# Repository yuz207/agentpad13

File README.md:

# agentpad13

A 13-key macropad for agentic work, designed from scratch: RP2040, USB-C, 12×1U + 1×2U hot-swap
keys, a clickable EC11 encoder, an analog tilt joystick, a capacitive-touch key, and 24 RGB LEDs
(per-key plus edge underglow) that an open Raw HID protocol drives to show what your agents are
doing — thinking, running, waiting, done, one key each.

## Build one

### → [Open the configurator](https://yuz207.github.io/agentpad13/configurator/site/)

Pick your options, turn the pad around in 3D, and get back an order sheet where every line links to
the exact file you upload to a fab or drop into a slicer. That is the way in. Prefer paper?
[`release/HOW-TO-ORDER.md`](release/HOW-TO-ORDER.md) is the same thing, static.

<p align="center"><sub>The shipping v5 board in the v2 case, straight from the CAD.</sub></p>

## What is where

```
release/            The bundle — everything you order, print or flash.
  HOW-TO-ORDER.md     The configurator's static form.
  RELEASE.md          What shipped and why, section by section.
  MANIFEST.md         Every file in the bundle with its md5 and byte count.
  hardware/           Board fab package, case, plate, bases, keycaps, toppers, gasket.
  firmware/           Flashable UF2s, BRING-UP.md, POLARITY-NOTE.md.
configurator/       The published site and its consumption assets; current outputs are copied from development.
firmware/           vial-qmk tree, simulations, conformance tests, BUILD.md.
docs/               The Raw HID protocol contract, and the design reviews.
```

Before you send anything to a fab, run `python3 manifest_selfverify.py` — it should print
**9/9 checks PASS**. Every listed file is present with the right hash, and nothing unlisted is
hiding in the bundle.

## Printed toppers already? Print them again

The v1 encoder knobs and stick caps are retired. The current release carries three Ø17.5 encoder
knob styles and three joystick toppers: a compact nub, restored TPU puck, and a conventional Ø12
topper paired with a TPU restrictor. Details are in [`release/RELEASE.md`](release/RELEASE.md) §(f).

## Status

- **PCB — complete.** v5_8, 84.2 × 100 mm, 2-layer, DRC clean, fab package ready to upload. It retains the v5.7 LED correction, adds the Ø4.0 TP5 solder landing, and factory-populates the encoder.
- **Case — complete.** v2.17: FR4 or printed plate, band in three sidewalls, printed tray.
- **Bases — complete.** Three optional printed bases; the case is finished without one.
- **Firmware — validated.** Emulator-booted and protocol-conformant. Flash `agentpad13.uf2`.
- **Configurator — live.** Static files: no build step, no network calls, no dependencies.

### AgentPad13 Direct OAI (experimental alternative)

The isolated `codex_oai` keymap is an experimental alternative for direct
Codex Desktop control. It is not Vial firmware and does not replace the normal,
recommended `release/firmware/prebuilt/agentpad13.uf2`. Codex Desktop talks to
this target directly—no helper, daemon, bridge, or Vial protocol—using the
locked `Codex Micro Lab OAI LED` identity (`303A:8360`, usage `FF00:61`, Report
ID 6, 64-byte reports).

The current unflashed candidate is
`release/firmware/prebuilt/agentpad13_codex_oai.uf2`, 93,696 bytes, SHA-256
`fcb50b2419419be43b7cf90b00a96b16063fcaf182bc24b9642d57e2e8adf54d`.
Start with the [keymap contract](firmware/loudest_micro/keymaps/codex_oai/README.md),
[source hand-off](firmware/CODEX-OAI-SOURCE.md), and
[Direct OAI build procedure](firmware/BUILD.md#agentpad13-direct-oai-experimental-alternative).
Run the complete host suite from the repository root:

```sh
python3 -m unittest discover -s firmware/tests/codex_oai -p 'test_*.py'
```

The checked-in [emulator capture](firmware/evidence/codex-oai-emulator.json)
and [current manifest](firmware/evidence/codex-oai-current-manifest.json) bind
that exact UF2 to the offline USB/protocol/LED checks. Physical validation is
still entirely PENDING; no install or flash occurred. Any future hardware
operation requires the literal authorization and observation record in the
[physical runbook](docs/codex-oai-physical-runbook.md).

## First power-on

Flash [`agentpad13.uf2`](release/firmware/prebuilt/agentpad13.uf2) — hold BOOTSEL and drag the file on. Then hold
SW14, the button in the back, for about a second and follow the 13 key LEDs: the board measures its
own joystick and stores the result. About 15 seconds, no host software, no reflash, once ever —
full procedure in [`release/firmware/BRING-UP.md`](release/firmware/BRING-UP.md). If an axis reads
backwards that is polarity, not calibration:
[`release/firmware/POLARITY-NOTE.md`](release/firmware/POLARITY-NOTE.md).

Firmware source is in [`firmware/loudest_micro/`](firmware/loudest_micro/); the exact Vial/QMK
build recipe and validation commands are in [`firmware/BUILD.md`](firmware/BUILD.md). The plain-QMK,
byte-reproducible build is [`agentpad13_reference.uf2`](release/firmware/prebuilt/agentpad13_reference.uf2).

## Licensing

- `release/hardware/` — **CERN-OHL-W-2.0** (PCB and case CAD).
- `firmware/` and `release/firmware/` — **GPL-2.0-or-later** (QMK/vial-qmk
  derivative), except `firmware/tests/conformance/protocol_oracle.py`, which is
  **MIT**. Corresponding source for the prebuilt UF2s = this tree built against
  [vial-qmk](https://github.com/vial-kb/vial-qmk) per `firmware/BUILD.md`.

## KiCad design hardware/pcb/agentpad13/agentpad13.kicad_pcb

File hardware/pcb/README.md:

# agentpad13 — PCB (v5, complete)

Finished, fabrication-ready 2-layer RP2040 macropad PCB. Designed in **KiCad 9**.

- **Outline:** 84.2 × 100 mm octagon (chamfered), 1.6 mm FR-4, 2 layers.
- **DRC:** clean — **0 violations, 0 unconnected** at a 0.152 mm / 6-mil standard
  fab tier (min via drill 0.20 mm).
- **Function:** 13 hot-swap keys (12×1U + 1×2U), EC11 encoder + push, analog
  2-axis tilt joystick (YTL YA13), TTP223 capacitive touch key, and a 24-LED
  SK6812 chain (14 reverse-mount top LEDs incl. 1 layer indicator + 10
  side/underglow LEDs) level-shifted for a 5 V VBUS rail. All SMD reflow parts
  are on the back (B.Cu); the joystick is a machine-placed through-hole part
  on the front.
- **v5 vs Rev A:** the encoder moved so its shaft centers on the case plate's
  encoder opening, the USB-C receptacle was flipped 180° so its mouth faces the
  case wall aperture, and the hand-solder PSP-slider joystick was replaced by
  the fab-placed YA13 tilt gimbal (LCSC C37323742) with datasheet-verified
  wiring — see `renders/js1_detail.png` and `../../firmware/POLARITY-NOTE.md`
  for the one-time axis/calibration config note.

## Board revision — v5_7 (current)

The published board is **v5_7**. It differs from **v5_6**, the revision the first
units were built from, by **two footprint rotations and nothing else**: the
bottom-edge underglow LEDs **LED20** and **LED21** were rotated 180° so they fire
*into* the board instead of off the edge. Same positions, same layer, same nets, no
part changes — both BOMs and the opaque SKU's pick-and-place file are byte-identical
to v5_6, and the translucent CPL differs in exactly those two rows (`Rot 0 → 180`).

Why they were wrong: the board generator applies each underglow LED's rotation and
*then* flips the part to the back copper, and that flip negates orientation. The two
pairs aimed along Y reversed; the left and right rails, aimed along X, survived. The
result was six of the ten side LEDs firing inward and four firing outward.

**`LED15`/`LED16`, beside the USB connector, still fire outward — that is
deliberate.** They wash the surface behind the pad and are kept that way by choice.
The shipping board is 8 inward / 2 outward.

If you have a board built from v5_6, nothing is broken and nothing needs reworking:
four of the ten underglow LEDs simply throw their light off the edge rather than
under the case.

## Files

```
agentpad13/                 the KiCad 9 project
  agentpad13.kicad_pcb      board
  agentpad13.kicad_sch      schematic
  agentpad13.kicad_pro      project
  fp-lib-table              footprint library table (KIPRJMOD-relative)
lib/                        vendored footprint libraries (see lib/LIBS.md)
BOM.csv                     full bill of materials (MPN / LCSC / DigiKey, pricing)
gerbers.zip                 bare-board manufacturing files (Gerbers + drill)
fabpack_opaque.zip          opaque SKU: gerbers + assembly CSVs + ORDERING.md
fabpack_translucent.zip     translucent SKU: gerbers + assembly CSVs + ORDERING.md
assembly/                   loose per-SKU assembly files
  cpl_opaque.csv            pick-and-place, opaque SKU      (90 placements)
  cpl_translucent.csv       pick-and-place, translucent SKU (110 placements)
  bom_opaque.csv            assembly BOM, opaque SKU
  bom_translucent.csv       assembly BOM, translucent SKU
  hand_solder_afterlist.csv the parts you hand-solder after the boards arrive
renders/                    top.png, bottom.png (v5_7), js1_detail.png (joystick
                            close-up; still the v5_6 plot — the revision changed
                            nothing at that end of the board)
```

## Two SKUs, one bare board

The bare PCB is **identical** for both SKUs — only which parts get placed differs:

| SKU | Top shell | Underglow (LED15-24 + C40-49) |
|---|---|---|
| **opaque** (Rev A default) | solid | not populated (DNP) |
| **translucent** | glowing diffuser | populated |

## Ordering

Upload **`gerbers.zip`** to the bare-board quote and the matching SKU's
`assembly/cpl_<sku>.csv` + `assembly/bom_<sku>.csv` to turnkey (consigned)
assembly — **single side** (bottom SMD; the joystick is a fab-placed
through-hole part). Each `fabpack_*.zip` bundles the Gerbers, that SKU's
assembly CSVs, and a full step-by-step `ORDERING.md` (board options, tier
guidance, DNP handling, pricing ballpark, and pre-order gates). The repo-root
`HOW-TO-ORDER.md` is the condensed walk-through.

**LED cut-outs are intentional:** the Edge.Cuts layer has 14 small internal
rounded-rectangle windows (one per top LED) so the reverse-mounted LEDs shine
through the board — not an outline error.

## Hand-soldered afterlist

The fab places everything else — including the JS1 joystick, a machine-placed
through-hole YA13 (its wiring is datasheet-verified; no metering needed). You
hand-solder (see `assembly/hand_solder_afterlist.csv`):

- **RE1** — EC11 rotary encoder + push (through-hole). Seat it flush.
- Optionally the 13 hot-swap sockets (SW1-13) and 2 tact switches (SW14/15) if you
  opt out of fab assembly for them — they are fab-placed by default.

At first power-on, if the stick drives the cursor opposite to your push, that is
the expected 180°-clocking polarity — a one-line config fix per axis, described
with the calibration note in `../../firmware/POLARITY-NOTE.md`.

## Firmware / GPIO note

The firmware pin map (`firmware/loudest_micro/`) matches the v5 board (identical
to Rev A v4 — the v5 changes needed zero firmware edits) and has been
validated — it boots in an RP2040 emulator and its Raw HID status protocol is
conformance-tested. See `firmware/FIRMWARE-V4-NOTES.md` and `firmware/tests/`.

## License

Hardware (schematic, PCB): **CERN-OHL-W-2.0**. Vendored footprint libraries keep
their upstream licenses (marbastlib: CERN-OHL-P v2; MX_V2: MIT) — see `lib/LIBS.md`.

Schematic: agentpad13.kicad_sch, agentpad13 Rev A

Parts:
C1, C2, C3, C4, C5, C6, C7, C8, C9, C10, C13, C20, C21, C22, C23, C24, C26, C27, C28, C29, C30, C31, C32, C33, C34, C35, C36, C37, C38, C39, C40, C41, C42, C43, C44, C45, C46, C47, C48, C49: 100n; C_0402_1005Metric; MPN CL05B104KO5NNNC; LCSC C1525
C11, C12, C14, C15: 1u; C_0402_1005Metric; MPN CL05A105KA5NNNC; LCSC C52923
C16, C17: 10u; C_0805_2012Metric; MPN CL21A106KOQNNNE; LCSC C15850
C18, C19: 15p; C_0402_1005Metric; MPN CL05C150JB5NNNC; LCSC C1548
C25: DNP; C_0402_1005Metric; MPN C_0402; JLC Basic; not fitted
D1: SD05C; D_SOD-323; MPN SD05C; LCSC C1884584; not fitted
F1: 750mA; Fuse_1812_4532Metric; MPN MF-MSMF075/24-2; LCSC C208467
FB1: 600R@100MHz; L_0402_1005Metric; MPN BLM15AG601SN1D; LCSC C76884
J1: USB-C; USB_C_Receptacle_HRO_TYPE-C-31-M-12; MPN TYPE-C-31-M-12; LCSC C165948
J2: EXPANSION; PinHeader_1x08_P2.54mm_Vertical; MPN PinHeader_1x08; JLC n/a; not fitted
JS1: YA13-FL7.4-B5Ka; YA13-FL7.4-B5Ka_C37323742; MPN YA13-FL7.4-B5Ka(45-10)-R-Y06; LCSC C37323742
LED1, LED2, LED3, LED4, LED5, LED6, LED7, LED8, LED9, LED10, LED11, LED12, LED13, LED14: SK6812MINI-E; LED_6028R; MPN SK6812MINI-E; LCSC C5149201
LED15, LED16, LED17, LED18, LED19, LED20, LED21, LED22, LED23, LED24: SK6812-SIDE; LED_WS2812_4020; MPN SK6812SIDE-A; LCSC C5378721
R1, R2: 5.1k; R_0402_1005Metric; MPN 0402WGF5101TCE; LCSC C25905
R3, R4: 27; R_0402_1005Metric; MPN 0402WGF270JTCE; LCSC C25100
R5, R6, R11, R12: 1k; R_0402_1005Metric; MPN 0402WGF1001TCE; LCSC C11702
R7: 10k; R_0402_1005Metric; MPN 0402WGF1002TCE; LCSC C25744
R8, R9: 4.7k; R_0402_1005Metric; MPN 0402WGF4701TCE; LCSC C25900
R10: 0R; R_0402_1005Metric; MPN 0402WGF0000TCE; LCSC C17168
RE1: EC11; RotaryEncoder_Alps_EC11E-Switch_Vertical_H20mm; MPN PEC11R-4215F-S0024; LCSC C143790
SW1, SW2, SW3, SW4, SW5, SW6, SW7, SW8, SW9, SW10, SW11, SW12, SW13: MX_Hotswap; SW_MX_HS_CPG151101S11_1u; MPN Kailh_CPG151101S11; LCSC C41430893
SW14: BOOT; SW_SPST_PTS645Sx43SMTR92; MPN PTS645SM43SMTR92 LFS; LCSC C221880
SW15: RESET; SW_SPST_PTS645Sx43SMTR92; MPN PTS645SM43SMTR92 LFS; LCSC C221880
TP1: SWCLK; TestPoint_Pad_D1.5mm; MPN TestPad; JLC n/a
TP2: SWDIO; TestPoint_Pad_D1.5mm; MPN TestPad; JLC n/a
TP3: 3V3; TestPoint_Pad_D1.5mm; MPN TestPad; JLC n/a
TP4: GND; TestPoint_Pad_D1.5mm; MPN TestPad; JLC n/a
TP5: TOUCHPAD; TestPoint_Pad_D1.5mm; MPN CopperPour; JLC n/a
U1: RP2040; QFN-56-1EP_7x7mm_P0.4mm_EP3.2x3.2mm; MPN RP2040; LCSC C2040
U2: W25Q128JVSIQ; SOIC-8_5.3x5.3mm_P1.27mm; MPN W25Q128JVSIQ; LCSC C97521
U3: AP2112K-3.3; SOT-23-5; MPN AP2112K-3.3TRG1; LCSC C51118
U4: USBLC6-2SC6; SOT-23-6; MPN USBLC6-2SC6; LCSC C7519
U5: SN74LVC1T45; SOT-23-6; MPN SN74LVC1T45DBVR; LCSC C7843
U6: TTP223; SOT-23-6; MPN TTP223-BA6; LCSC C42422127
Y1: 12MHz ABM8-272-T3; Crystal_SMD_3225-4Pin_3.2x2.5mm; MPN ABM8-272-T3; LCSC C20625731

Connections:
+1V1: C7.1, C8.1, C12.1, U1.23 (DVDD), U1.45 (VREG_VOUT), U1.50 (DVDD)
+3V3: C1.1, C2.1, C3.1, C4.1, C5.1, C6.1, C10.1, C11.1, C13.1, C15.1, C17.1, C20.1, C22.1, FB1.1, J2.1, JS1.1 (XA), JS1.4 (YA), R7.1, R8.1, R9.1, TP3.1, U1.1 (IOVDD), U1.10 (IOVDD), U1.22 (IOVDD), U1.33 (IOVDD), U1.42 (IOVDD), U1.44 (VREG_VIN), U1.48 (USB_VDD), U1.49 (IOVDD), U2.8 (VCC), U3.5 (VOUT), U5.1 (VCCA), U5.5 (DIR), U6.5 (VDD)
+5V: C14.1, C16.1, C21.1, C26.1, C27.1, C28.1, C29.1, C30.1, C31.1, C32.1, C33.1, C34.1, C35.1, C36.1, C37.1, C38.1, C39.1, C40.1, C41.1, C42.1, C43.1, C44.1, C45.1, C46.1, C47.1, C48.1, C49.1, D1.2 (K), F1.2, J2.8, LED1.1 (VDD), LED2.1 (VDD), LED3.1 (VDD), LED4.1 (VDD), LED5.1 (VDD), LED6.1 (VDD), LED7.1 (VDD), LED8.1 (VDD), LED9.1 (VDD), LED10.1 (VDD), LED11.1 (VDD), LED12.1 (VDD), LED13.1 (VDD), LED14.1 (VDD), LED15.2 (VDD), LED16.2 (VDD), LED17.2 (VDD), LED18.2 (VDD), LED19.2 (VDD), LED20.2 (VDD), LED21.2 (VDD), LED22.2 (VDD), LED23.2 (VDD), LED24.2 (VDD), U3.1 (VIN), U3.3 (EN), U4.5 (VBUS), U5.6 (VCCB)
ADC_AVDD: C9.1, FB1.2, U1.43 (ADC_AVDD)
BOOTSEL: R6.2, SW14.1
CC1: J1.A5 (CC1), R1.1
CC2: J1.B5 (CC2), R2.1
DM: R4.2, U1.46 (USB_DM)
DP: R3.2, U1.47 (USB_DP)
ENC_A: RE1.A, U1.16 (GPIO13)
ENC_B: RE1.B, U1.17 (GPIO14)
ENC_SW: RE1.S1, U1.18 (GPIO15)
GND: C1.2, C2.2, C3.2, C4.2, C5.2, C6.2, C7.2, C8.2, C9.2, C10.2, C11.2, C12.2, C13.2, C14.2, C15.2, C16.2, C17.2, C18.2, C19.2, C20.2, C21.2, C22.2, C23.2, C24.2, C25.2, C26.2, C27.2, C28.2, C29.2, C30.2, C31.2, C32.2, C33.2, C34.2, C35.2, C36.2, C37.2, C38.2, C39.2, C40.2, C41.2, C42.2, C43.2, C44.2, C45.2, C46.2, C47.2, C48.2, C49.2, D1.1 (A), J1.A1 (GND), J1.A12 (GND), J1.B1 (GND), J1.B12 (GND), J1.S1 (SHIELD), J2.2, JS1.3 (XB), JS1.6 (YB), JS1.MP1, JS1.MP2, JS1.MP3, JS1.MP4, LED1.4 (VSS), LED2.4 (VSS), LED3.4 (VSS), LED4.4 (VSS), LED5.4 (VSS), LED6.4 (VSS), LED7.4 (VSS), LED8.4 (VSS), LED9.4 (VSS), LED10.4 (VSS), LED11.4 (VSS), LED12.4 (VSS), LED13.4 (VSS), LED14.4 (VSS), LED15.4 (VSS), LED16.4 (VSS), LED17.4 (VSS), LED18.4 (VSS), LED19.4 (VSS), LED20.4 (VSS), LED21.4 (VSS), LED22.4 (VSS), LED23.4 (VSS), LED24.4 (VSS), R1.2, R2.2, R10.2, RE1.C, RE1.S2, SW1.2, SW2.2, SW3.2, SW4.2, SW5.2, SW6.2, SW7.2, SW8.2, SW9.2, SW10.2, SW11.2, SW12.2, SW13.2, SW14.2, SW15.2, TP4.1, U1.19 (TESTEN), U1.57 (GND), U2.4 (GND), U3.2 (GND), U4.2 (GND), U5.2 (GND), U6.2 (VSS), U6.6 (TOG), Y1.2, Y1.4
GP20: J2.5, U1.31 (GPIO20)
GP21: J2.6, U1.36 (GPIO24)
GP28: J2.7, U1.40 (GPIO28_ADC2)
JOY_X: JS1.2 (XW), R11.1
JOY_X_ADC: C23.1, R11.2, U1.38 (GPIO26_ADC0)
JOY_Y: JS1.5 (YW), R12.1
JOY_Y_ADC: C24.1, R12.2, U1.39 (GPIO27_ADC1)
PORT_DM: J1.A7 (DN1), J1.B7 (DN2), U4.4 (IO2)
PORT_DP: J1.A6 (DP1), J1.B6 (DP2), U4.6 (IO1)
QSPI_CLK: U1.52 (QSPI_SCLK), U2.6 (CLK)
QSPI_CS: R6.1, U1.56 (QSPI_SS_N), U2.1 (~CS)
QSPI_SD0: U1.53 (QSPI_SD0), U2.5 (DI_IO0)
QSPI_SD1: U1.55 (QSPI_SD1), U2.2 (DO_IO1)
QSPI_SD2: U1.54 (QSPI_SD2), U2.3 (~WP_IO2)
QSPI_SD3: U1.51 (QSPI_SD3), U2.7 (~HOLD_IO3)
RGB_D00: LED1.3 (DIN), U5.4 (B)
RGB_D01: LED1.2 (DOUT), LED2.3 (DIN)
RGB_D02: LED2.2 (DOUT), LED3.3 (DIN)
RGB_D03: LED3.2 (DOUT), LED4.3 (DIN)
RGB_D04: LED4.2 (DOUT), LED5.3 (DIN)
RGB_D05: LED5.2 (DOUT), LED6.3 (DIN)
RGB_D06: LED6.2 (DOUT), LED7.3 (DIN)
RGB_D07: LED7.2 (DOUT), LED8.3 (DIN)
RGB_D08: LED8.2 (DOUT), LED9.3 (DIN)
RGB_D09: LED9.2 (DOUT), LED10.3 (DIN)
RGB_D10: LED10.2 (DOUT), LED11.3 (DIN)
RGB_D11: LED11.2 (DOUT), LED12.3 (DIN)
RGB_D12: LED12.2 (DOUT), LED13.3 (DIN)
RGB_D13: LED13.2 (DOUT), LED14.3 (DIN)
RGB_D14: LED14.2 (DOUT), LED15.1 (DIN)
RGB_D15: LED15.3 (DOUT), LED16.1 (DIN)
RGB_D16: LED16.3 (DOUT), LED17.1 (DIN)
RGB_D17: LED17.3 (DOUT), LED18.1 (DIN)
RGB_D18: LED18.3 (DOUT), LED19.1 (DIN)
RGB_D19: LED19.3 (DOUT), LED20.1 (DIN)
RGB_D20: LED20.3 (DOUT), LED21.1 (DIN)
RGB_D21: LED21.3 (DOUT), LED22.1 (DIN)
RGB_D22: LED22.3 (DOUT), LED23.1 (DIN)
RGB_D23: LED23.3 (DOUT), LED24.1 (DIN)
RGB_MCU: U1.28 (GPIO17), U5.3 (A)
RUN: R7.2, SW15.1, U1.26 (RUN)
SCL: J2.4, R9.2, U1.30 (GPIO19)
SDA: J2.3, R8.2, U1.29 (GPIO18)
SW1: SW1.1, U1.15 (GPIO12)
SW2: SW2.1, U1.12 (GPIO9)
SW3: SW3.1, U1.7 (GPIO5)
SW4: SW4.1, U1.4 (GPIO2)
SW5: SW5.1, U1.14 (GPIO11)
SW6: SW6.1, U1.11 (GPIO8)
SW7: SW7.1, U1.6 (GPIO4)
SW8: SW8.1, U1.3 (GPIO1)
SW9: SW9.1, U1.13 (GPIO10)
SW10: SW10.1, U1.9 (GPIO7)
SW11: SW11.1, U1.5 (GPIO3)
SW12: SW12.1, U1.2 (GPIO0)
SW13: SW13.1, U1.8 (GPIO6)
SWCLK: TP1.1, U1.24 (SWCLK)
SWDIO: TP2.1, U1.25 (SWDIO)
TOUCH_AHLB: R10.1, U6.4 (AHLB)
TOUCH_OUT: U1.27 (GPIO16), U6.1 (Q)
TOUCH_PAD: C25.1, TP5.1, U6.3 (I)
USB_DM: R4.1, U4.3 (IO2)
USB_DP: R3.1, U4.1 (IO1)
VBUS: F1.1, J1.A4 (VBUS), J1.A9 (VBUS), J1.B4 (VBUS), J1.B9 (VBUS)
XIN: C18.1, U1.20 (XIN), Y1.1
XOUT: R5.1, U1.21 (XOUT)
XOUT_XTAL: C19.1, R5.2, Y1.3

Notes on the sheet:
agentpad13 Rev A flat schematic (auto-generated). Connectivity is by net-name labels; footprints bound at layout.

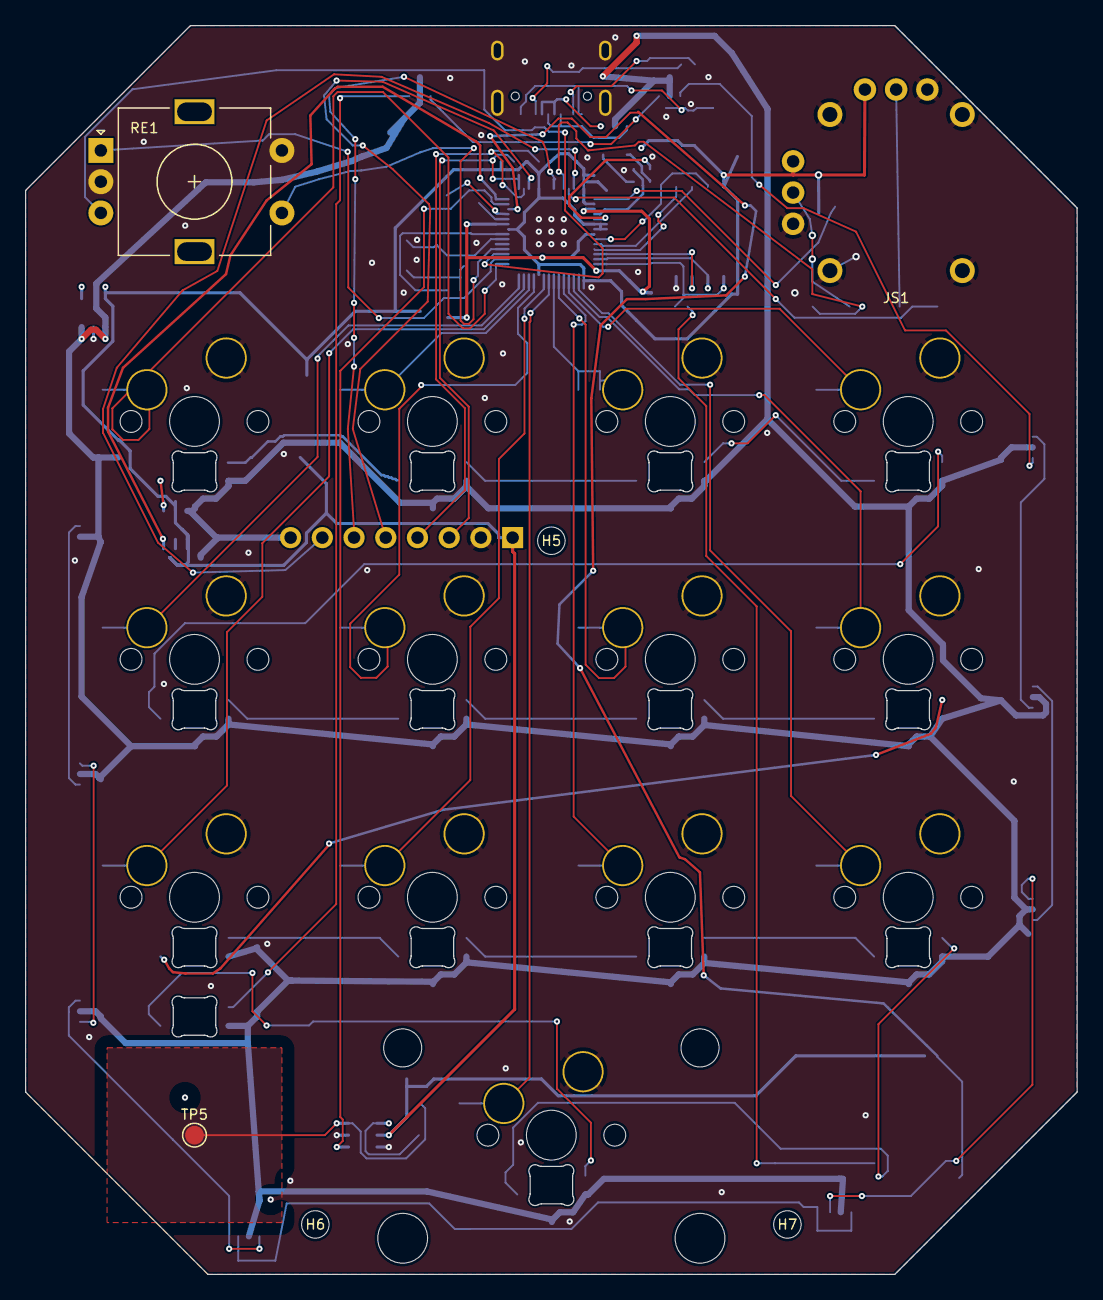
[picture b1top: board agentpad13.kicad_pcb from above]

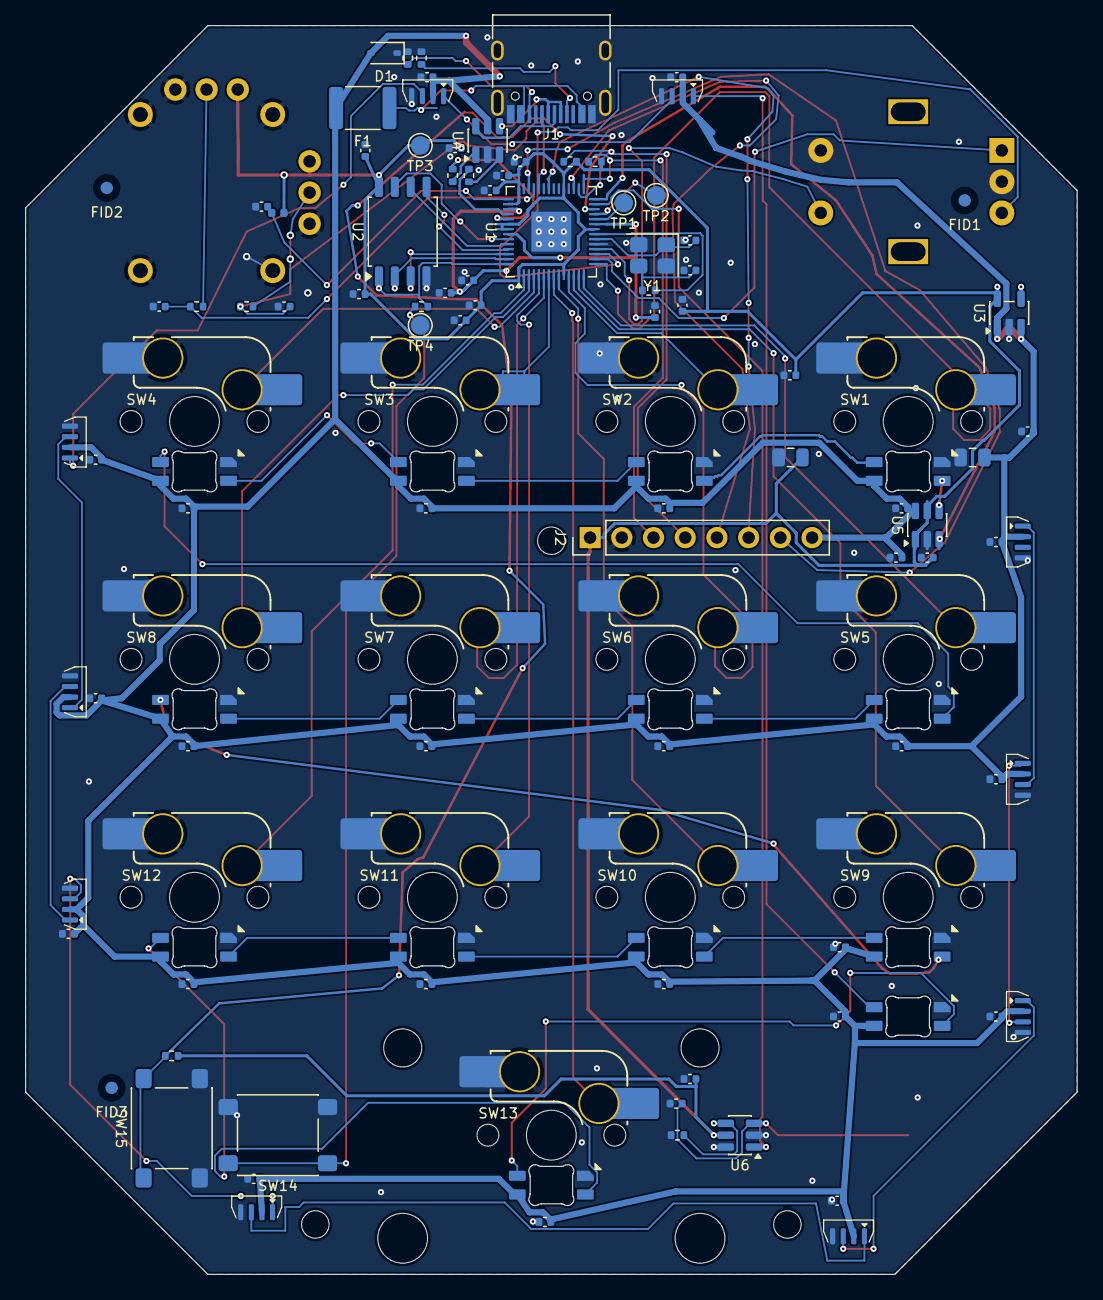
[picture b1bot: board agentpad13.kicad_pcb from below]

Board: 2 copper layers, 84.2 x 100.0 mm, 126 parts (119 on the bottom side), 80 nets.

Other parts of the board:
FID1, FID2, FID3: Fiducial_1mm_Mask2mm
H5, H6, H7: (no value)
STAB1: MX_2u_stab; STAB_MX_2u

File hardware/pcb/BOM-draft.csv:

References,Qty,Value,Description,Footprint_intended,MPN,LCSC,JLC_Tier,DNP,Verify_Flags
"C1,C2,C3,C4,C5,C6,C7,C8,C9,C10,C13,C20,C21,C22,C23,C24,C26,C27,C28,C29,C30,C31,C32,C33,C34,C35,C36,C37,C38,C39,C40,C41,C42,C43,C44,C45,C46,C47,C48,C49",40,100n,"100nF X7R bypass / decoupling / RC, 0402",Capacitor_SMD:C_0402_1005Metric,CL05B104KO5NNNC,C1525,Basic,,
"C11,C12,C14,C15",4,1u,"1uF X5R, 0402 (RP2040 VREG + LDO in/out)",Capacitor_SMD:C_0402_1005Metric,CL05A105KA5NNNC,C52923,Basic,,
"C16,C17",2,10u,"10uF X5R, 0805 (rail bulk)",Capacitor_SMD:C_0805_2012Metric,CL21A106KOQNNNE,C15850,Basic,,
"C18,C19",2,15p,"15pF C0G crystal load, 0402",Capacitor_SMD:C_0402_1005Metric,CL05C150JB5NNNC,C1548,Basic,,
C25,1,DNP,"touch sensitivity cap (DNP, tune 0-50pF)",Capacitor_SMD:C_0402_1005Metric,C_0402,,Basic,DNP,LCSC# to verify at order
D1,1,SD05C,"VBUS TVS (optional, DNP)",Diode_SMD:D_SOD-323,SD05C,C907858,Extended,DNP,
F1,1,500mA,PTC polyfuse 500mA hold,Fuse:Fuse_1812_4532Metric,MF-MSMF050-2,C17313,Extended,,
J1,1,USB-C,USB-C 2.0 receptacle,Connector_USB:USB_C_Receptacle_HRO_TYPE-C-31-M-12,TYPE-C-31-M-12,C165948,Extended,,
J2,1,EXPANSION,I2C(GP18/19)+3V3+GND+spares GP20/21/GP28+5V,Connector_PinHeader_2.54mm:PinHeader_1x08_P2.54mm_Vertical,PinHeader_1x08,,n/a,,LCSC# to verify at order
JS1,1,PSP-Slider,2-axis planar joystick (Phase-1 select),loudest:Joystick_PSP_Slider  # TBD Phase-1 part select,Adafruit-444_or_clone,,n/a(hand-solder),,footprint/part TBD at layout; LCSC# to verify at order
"LED1,LED2,LED3,LED4,LED5,LED6,LED7,LED8,LED9,LED10,LED11,LED12,LED13,LED14",14,SK6812MINI-E,"RGB LED reverse-mount, per-key + layer indicator",marbastlib:LED_SK6812MINI-E_ReverseMount  # TBD bind at layout,SK6812MINI-E,C5149201,Standard-Only,,footprint/part TBD at layout; JLC tier verify/back-side
"LED15,LED16,LED17,LED18,LED19,LED20,LED21,LED22,LED23,LED24",10,SK6812-SIDE,"RGB LED side-firing 4020, underglow",marbastlib:LED_SK6812-SIDE_4020  # TBD bind at layout,SK6812-SIDE-A,C_TBD_verify,Standard/Extended-verify,,footprint/part TBD at layout; LCSC# to verify at order; JLC tier verify/back-side
"R1,R2",2,5.1k,"5.1k 1% USB-C CC pulldown, 0402",Resistor_SMD:R_0402_1005Metric,0402WGF5101TCE,C25905,Basic,,
"R3,R4",2,27,"27R USB D+/D- series, 0402",Resistor_SMD:R_0402_1005Metric,0402WGF270JTCE,C25100,Basic,,
"R5,R6,R11,R12",4,1k,"1k series (XOUT / BOOTSEL / joystick RC), 0402",Resistor_SMD:R_0402_1005Metric,0402WGF1001TCE,C11702,Basic,,
R7,1,10k,"10k RUN pull-up, 0402",Resistor_SMD:R_0402_1005Metric,0402WGF1002TCE,C25744,Basic,,
"R8,R9",2,4.7k,"4.7k I2C SDA/SCL pull-up, 0402",Resistor_SMD:R_0402_1005Metric,0402WGF4701TCE,C25900,Basic,,
R10,1,0R,"0R AHLB strap (GND=active-high), 0402",Resistor_SMD:R_0402_1005Metric,0402WGF0000TCE,C17168,Basic,,
RE1,1,EC11,"rotary encoder + push (A/B=GP13/14, SW=GP15)",Rotary_Encoder:RotaryEncoder_Alps_EC11E-Switch_Vertical_H20mm  # TBD bind at layout,PEC11R-4215F-S0024,C143790,n/a(hand-solder),,footprint/part TBD at layout; LCSC retail OOS 2026-07 - alt source
"SW1,SW2,SW3,SW4,SW5,SW6,SW7,SW8,SW9,SW10,SW11,SW12,SW13",13,MX_Hotswap,"MX hotswap key switch, direct-pin GP0-12 (dual-socket combined FP)",marbastlib-mx:SW_MX_HS_Combined_pre-mirrored  # TBD bind at layout,Kailh_CPG151101S11,C2803348,Standard-Only(back),,footprint/part TBD at layout; JLC tier verify/back-side; LCSC retail OOS 2026-07 - alt source
SW14,1,BOOT,BOOTSEL tact,Button_Switch_SMD:SW_SPST_PTS645  # generic tact,TS-1187A,C318884,Basic,,
SW15,1,RESET,RESET tact,Button_Switch_SMD:SW_SPST_PTS645  # generic tact,TS-1187A,C318884,Basic,,
TP1,1,SWCLK,SWD test pad,TestPoint:TestPoint_Pad_D1.5mm,TestPad,,n/a,,LCSC# to verify at order
TP2,1,SWDIO,SWD test pad,TestPoint:TestPoint_Pad_D1.5mm,TestPad,,n/a,,LCSC# to verify at order
TP3,1,3V3,power test pad,TestPoint:TestPoint_Pad_D1.5mm,TestPad,,n/a,,LCSC# to verify at order
TP4,1,GND,ground test pad,TestPoint:TestPoint_Pad_D1.5mm,TestPad,,n/a,,LCSC# to verify at order
TP5,1,TOUCHPAD,14x14 sensing copper pour,TestPoint:TestPoint_Pad_D1.5mm,CopperPour,,n/a,,LCSC# to verify at order
U1,1,RP2040,"Dual Cortex-M0+ MCU, QFN-56 (RPi minimal design)",Package_DFN_QFN:QFN-56-1EP_7x7mm_P0.4mm_EP3.2x3.2mm,RP2040,C2040,Extended,,
U2,1,W25Q128JVSIQ,16 MB QSPI flash,Package_SO:SOIC-8_5.23x5.23mm_P1.27mm,W25Q128JVSIQ,C97521,Extended,,
U3,1,AP2112K-3.3,3.3V 600mA LDO,Package_TO_SOT_SMD:SOT-23-5,AP2112K-3.3TRG1,C51118,Extended,,
U4,1,USBLC6-2SC6,USB ESD array,Package_TO_SOT_SMD:SOT-23-6,USBLC6-2SC6,C7519,Extended,,
U5,1,SN74LVC1T45,"1-bit level shifter (A=3V3 GP17, B=5V LEDs, DIR=A->B)",Package_TO_SOT_SMD:SOT-23-6,SN74LVC1T45DBVR,C7843,Extended,,
U6,1,TTP223,"cap touch (OUT->GP16, TOG=GND direct mode)",Package_TO_SOT_SMD:SOT-23-6,TTP223-BA6,C80757,Extended,,
Y1,1,12MHz ABM8-272-T3,12 MHz 10pF crystal (RPi guide),Crystal:Crystal_SMD_Abracon_ABM8-4Pin_3.2x2.5mm,ABM8-272-T3,C20625731,Extended,,

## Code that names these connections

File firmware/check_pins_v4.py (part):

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     MATRIX_INPUT_PRESSED_STATE stays undefined.
  2. keyboard.json encoder / ws2812 / joystick pins == the table.
  3. No firmware reference to any spare/NC GPIO (GP18-GP25, GP28, GP29) -
     including the "GP21" J2 net-name trap: that NET is silicon GPIO24 and
     must never appear in firmware as a GPIO number.
  4. Source scan: every GPnn token in the keyboard C sources is one of the
     pins the table assigns to firmware.
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
# Reporting labels for positions with no scanned pin, so a `null` that is
# deliberate does not print as "unused".
MATRIX_LABELS = {(3, 2): "TOUCH_OUT (GP16, out of matrix by design)"}

# GPIOs firmware must never reference: I2C spares to the DNP J2 header
# (GP18 SDA / GP19 SCL / GP20 / GP28) plus every NC pad (GPIO21/22/23/25/29)
# and GPIO24 - the trap: the J2 net NAMED "GP21" is silicon GPIO24.
FORBIDDEN = {f"GP{n}" for n in (18, 19, 20, 21, 22, 23, 24, 25, 28, 29)}

ALLOWED = set(TABLE.values())
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            check(f"{source_name}: [{r},{c}] {label} = {want or 'null'}",
                  got == want, f"got {got}")
    enc = cfg["encoder"]["rotary"][0]
    check(f"{source_name}: encoder pin_a ENC_A = {TABLE['ENC_A']}",
          enc["pin_a"] == TABLE["ENC_A"], f"got {enc['pin_a']}")
    check(f"{source_name}: encoder pin_b ENC_B = {TABLE['ENC_B']}",
          enc["pin_b"] == TABLE["ENC_B"], f"got {enc['pin_b']}")
    check(f"{source_name}: ws2812 pin RGB_MCU = {TABLE['RGB_MCU']}",
          cfg["ws2812"]["pin"] == TABLE["RGB_MCU"], f"got {cfg['ws2812']['pin']}")
    axes = cfg["joystick"]["axes"]
    check(f"{source_name}: joystick x JOY_X_ADC = {TABLE['JOY_X_ADC']}",
          axes["x"]["input_pin"] == TABLE["JOY_X_ADC"], f"got {axes['x']['input_pin']}")
    check(f"{source_name}: joystick y JOY_Y_ADC = {TABLE['JOY_Y_ADC']}",
          axes["y"]["input_pin"] == TABLE["JOY_Y_ADC"], f"got {axes['y']['input_pin']}")
    # Forbidden-pin sweep over the whole config. Documentation keys ("$..."
    # comments) may legitimately NAME spare pins while explaining that they
    # are unused, so they are stripped: only configuration values count.
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    """
    print("-- touch (GP16) handled outside the matrix")
    src = (KEYBOARD_DIR / "loudest_micro.c").read_text()
    check(f"loudest_micro.c binds TOUCH_PIN to {TABLE['TOUCH_OUT']}",
          re.search(r"#define\s+TOUCH_PIN\s+" + TABLE["TOUCH_OUT"] + r"\b", src) is not None)
    check("loudest_micro.c declares the touch input ACTIVE-HIGH "
          "(TOUCH_PRESSED_STATE 1; board strap R10 TOUCH_AHLB->GND)",
          re.search(r"#define\s+TOUCH_PRESSED_STATE\s+1\b", src) is not None)
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    stray = sorted(src_pins - ALLOWED)
    check(f"sources reference only table-assigned pins ({sorted(src_pins)})",
          not stray, f"stray pins {stray}")
    check("sources reference no forbidden pin (incl. the GP21=GPIO24 net-name trap)",
          not (src_pins & FORBIDDEN), f"found {sorted(src_pins & FORBIDDEN)}")

    if args.qmk_info:
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        assert_pin_config(info, f"qmk info ({args.qmk_info.name})")
        print("-- resolved build config extras")
        check("qmk info: WS2812_DI_PIN resolves from ws2812.pin",
              info.get("ws2812", {}).get("pin") == TABLE["RGB_MCU"])
        check("qmk info: processor is RP2040",
              info.get("processor") == "RP2040", f"got {info.get('processor')}")

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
